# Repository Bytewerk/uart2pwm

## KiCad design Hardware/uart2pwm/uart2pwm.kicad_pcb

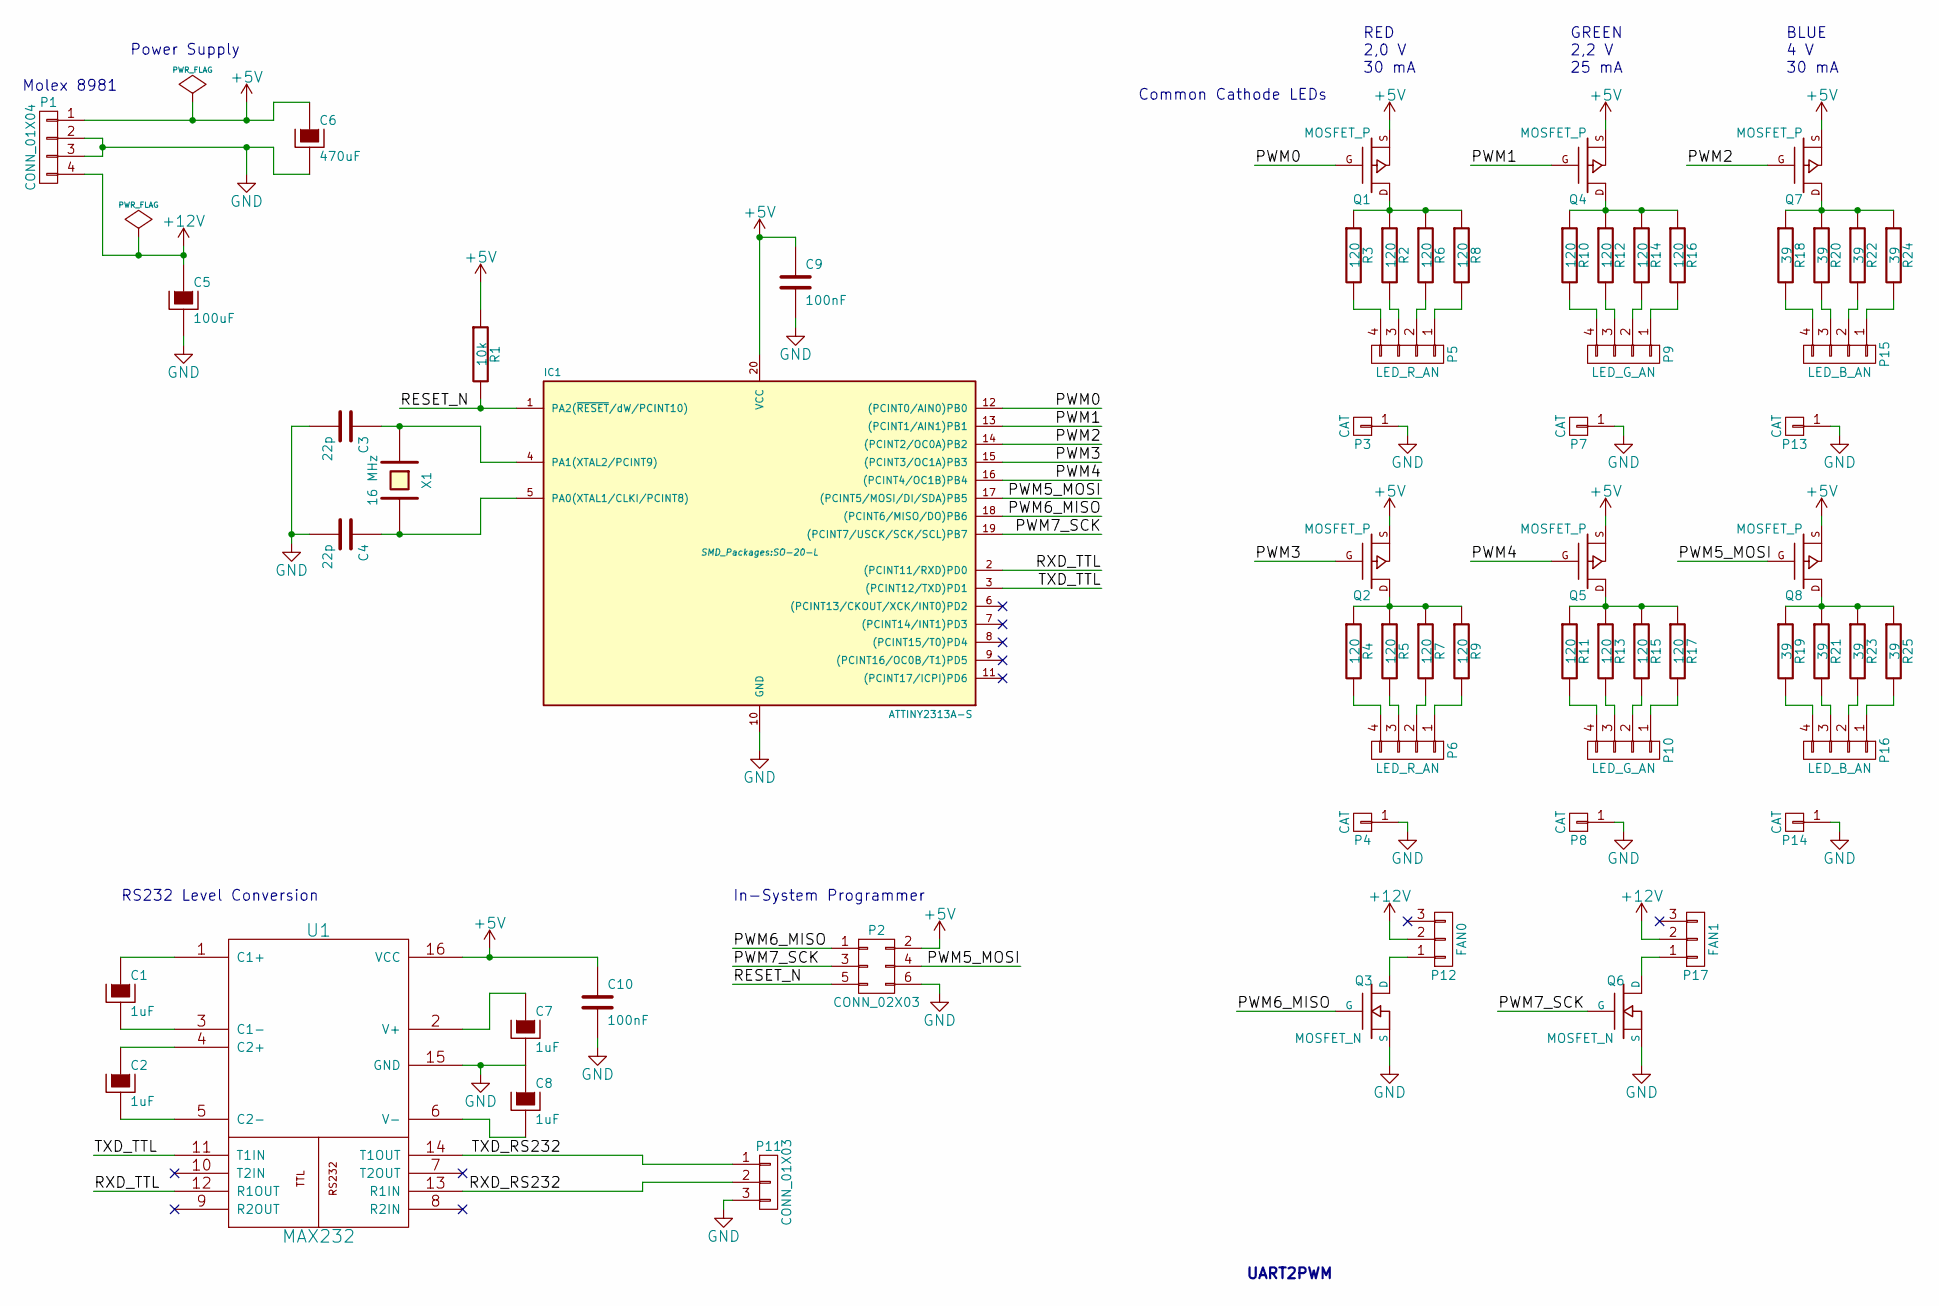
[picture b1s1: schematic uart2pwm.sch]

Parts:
C1, C2, C7, C8: 1uF; C_0805
C3, C4: 22p; SMD-0603
C5: 100uF; Elko_vert_11.5x8mm_RM3.5
C6: 470uF; Elko_vert_11.5x8mm_RM3.5
C9, C10: 100nF; SMD-0603
IC1: ATTINY2313A-S; SO-20-L
P1: CONN_01X04; MOLEX_8981_4Pin
P2: CONN_02X03; Pin_Header_Straight_2x03
P3, P4, P7, P8, P13, P14: CAT; Pin_Header_Straight_1x01
P5, P6: LED_R_AN; Pin_Header_Straight_2x02
P9, P10: LED_G_AN; Pin_Header_Straight_2x02
P11: CONN_01X03; Pin_Header_Straight_1x03
P12: FAN0; Pin_Header_Straight_1x03
P15, P16: LED_B_AN; Pin_Header_Straight_2x02
P17: FAN1; Pin_Header_Straight_1x03
Q1, Q2, Q4, Q5, Q7, Q8: MOSFET_P; SOT-23-GDS
Q3, Q6: MOSFET_N; SOT-23-GDS
R1: 10k; SMD-0603
R2, R3, R4, R5, R6, R7, R8, R9, R10, R11, R12, R13, R14, R15, R16, R17: 120; SMD-0603
R18, R19, R20, R21, R22, R23, R24, R25: 39; SMD-0603
U1: MAX232; DIP-16__300
X1: 16 MHz; Crystal_HC49-SD_SMD

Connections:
+5V: C6.1, C9.1, C10.1, IC1.20 (VCC), P1.1, P2.2, Q1.S, Q2.S, Q4.S, Q5.S, Q7.S, Q8.S, R1.1, U1.16 (VCC)
+12V: C5.1, P1.4, P12.2, P17.2
/PWM0: IC1.12 ((PCINT0/AIN0)PB0), Q1.G
/PWM1: IC1.13 ((PCINT1/AIN1)PB1), Q4.G
/PWM2: IC1.14 ((PCINT2/OC0A)PB2), Q7.G
/PWM3: IC1.15 ((PCINT3/OC1A)PB3), Q2.G
/PWM4: IC1.16 ((PCINT4/OC1B)PB4), Q5.G
/PWM5_MOSI: IC1.17 ((PCINT5/MOSI/DI/SDA)PB5), P2.4, Q8.G
/PWM6_MISO: IC1.18 ((PCINT6/MISO/DO)PB6), P2.1, Q3.G
/PWM7_SCK: IC1.19 ((PCINT7/USCK/SCK/SCL)PB7), P2.3, Q6.G
/RESET_N: IC1.1 (PA2(~RESET~/dW/PCINT10)), P2.5, R1.2
/RXD_RS232: P11.2, U1.13 (R1IN)
/RXD_TTL: IC1.2 ((PCINT11/RXD)PD0), U1.12 (R1OUT)
/TXD_RS232: P11.1, U1.14 (T1OUT)
/TXD_TTL: IC1.3 ((PCINT12/TXD)PD1), U1.11 (T1IN)
GND: C3.2, C4.2, C5.2, C6.2, C7.2, C8.1, C9.2, C10.2, IC1.10 (GND), P1.2, P1.3, P2.6, P3.1, P4.1, P7.1, P8.1, P11.3, P13.1, P14.1, Q3.S, Q6.S, U1.15 (GND)
unnamed: C1.1, U1.1 (C1+)
unnamed: C1.2, U1.3 (C1-)
unnamed: C2.1, U1.4 (C2+)
unnamed: C2.2, U1.5 (C2-)
unnamed: C3.1, IC1.4 (PA1(XTAL2/PCINT9)), X1.1
unnamed: C4.1, IC1.5 (PA0(XTAL1/CLKI/PCINT8)), X1.2
unnamed: C7.1, U1.2 (V+)
unnamed: C8.2, U1.6 (V-)
unnamed: P5.1, R8.2
unnamed: P5.2, R6.2
unnamed: P5.3, R2.2
unnamed: P5.4, R3.2
unnamed: P6.1, R9.2
unnamed: P6.2, R7.2
unnamed: P6.3, R5.2
unnamed: P6.4, R4.2
unnamed: P9.1, R16.2
unnamed: P9.2, R14.2
unnamed: P9.3, R12.2
unnamed: P9.4, R10.2
unnamed: P10.1, R17.2
unnamed: P10.2, R15.2
unnamed: P10.3, R13.2
unnamed: P10.4, R11.2
unnamed: P12.1, Q3.D
unnamed: P15.1, R24.2
unnamed: P15.2, R22.2
unnamed: P15.3, R20.2
unnamed: P15.4, R18.2
unnamed: P16.1, R25.2
unnamed: P16.2, R23.2
unnamed: P16.3, R21.2
unnamed: P16.4, R19.2
unnamed: P17.1, Q6.D
unnamed: Q1.D, R2.1, R3.1, R6.1, R8.1
unnamed: Q2.D, R4.1, R5.1, R7.1, R9.1
unnamed: Q4.D, R10.1, R12.1, R14.1, R16.1
unnamed: Q5.D, R11.1, R13.1, R15.1, R17.1
unnamed: Q7.D, R18.1, R20.1, R22.1, R24.1
unnamed: Q8.D, R19.1, R21.1, R23.1, R25.1

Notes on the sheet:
Power Supply
Common Cathode LEDs
In-System Programmer
RS232 Level Conversion
Molex 8981
RED 2,0 V 30 mA
GREEN 2,2 V 25 mA
BLUE 4 V 30 mA
UART2PWM

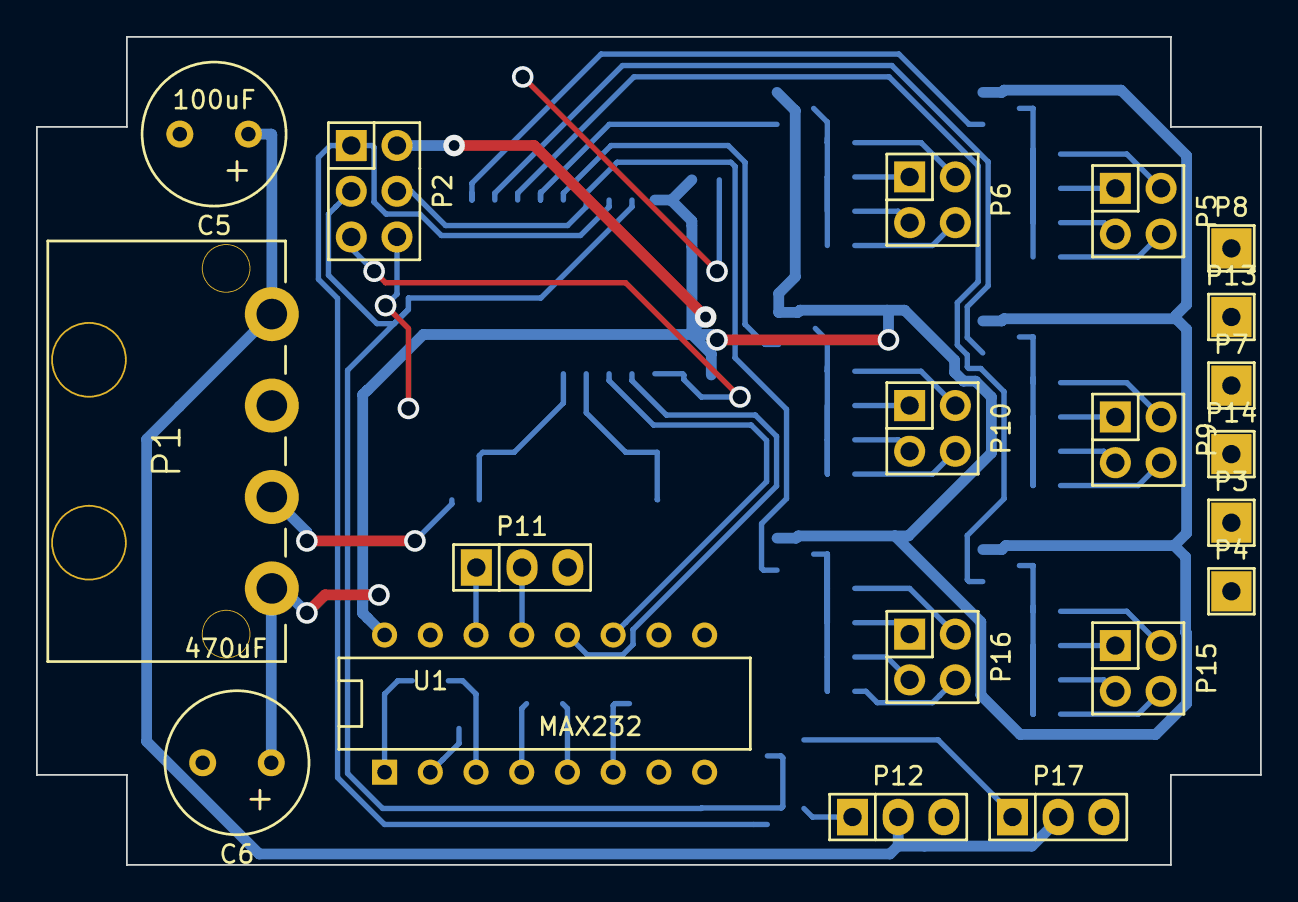
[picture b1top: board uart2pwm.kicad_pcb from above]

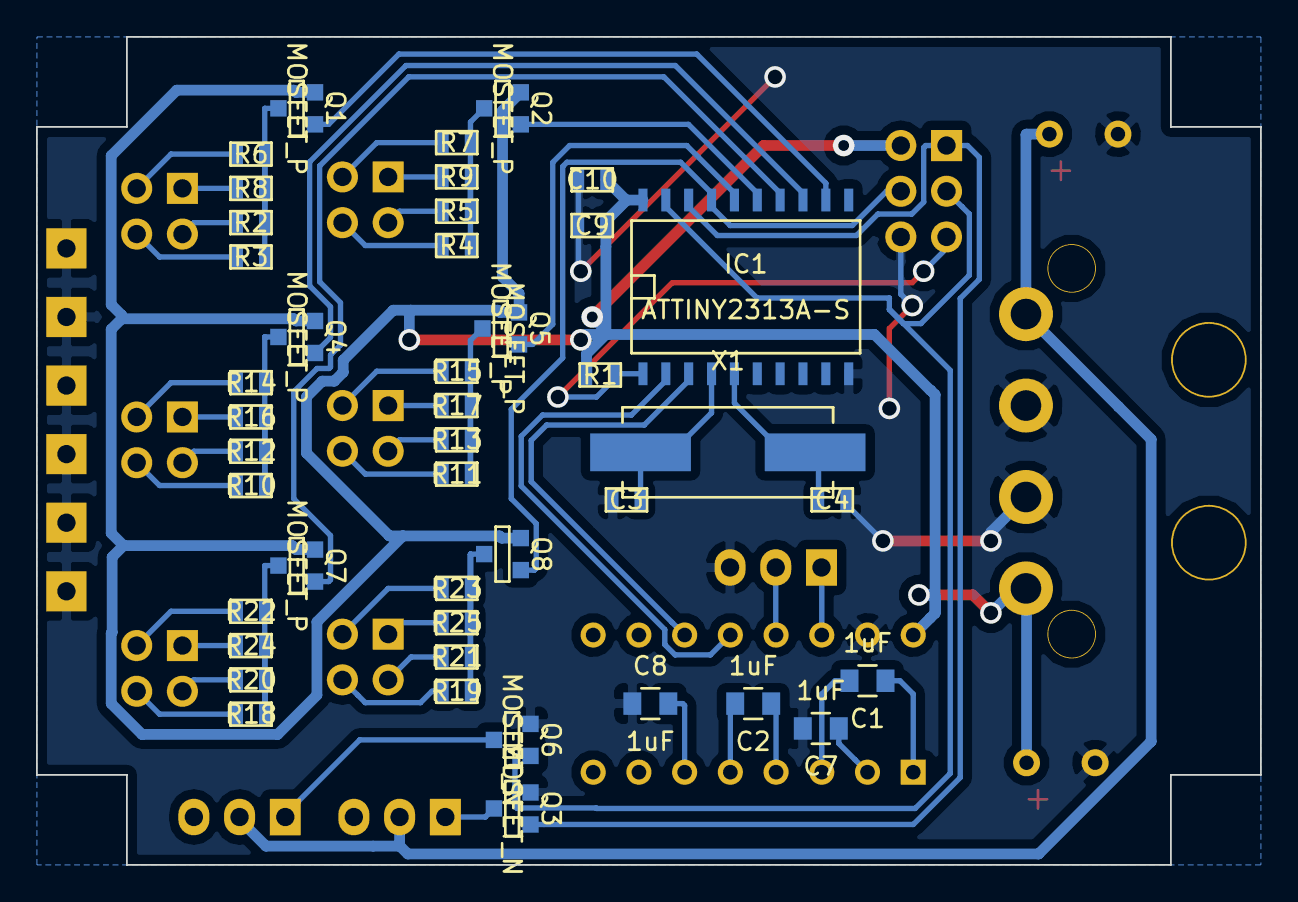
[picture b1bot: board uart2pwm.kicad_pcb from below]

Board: 2 copper layers, 68.0 x 46.0 mm, 63 parts (43 on the bottom side), 56 nets.

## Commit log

2015-03-22 Shell script for setting colors
2015-03-22 Added the RainbowPython lib with an example
2015-03-22 Escape the escape-sequence, if the user wants to send it
2015-03-22 Handle unknown characters in the protocol decoder
2015-03-22 Firmware code cleanup
2015-03-23 removed old set_led_brightness call
2015-03-23 added some timeout to the RainbowPython example
2015-03-23 First revision of the board schematic
2015-03-26 Schematic complete; Placement started
2015-04-04 Finalized first hardware revision
